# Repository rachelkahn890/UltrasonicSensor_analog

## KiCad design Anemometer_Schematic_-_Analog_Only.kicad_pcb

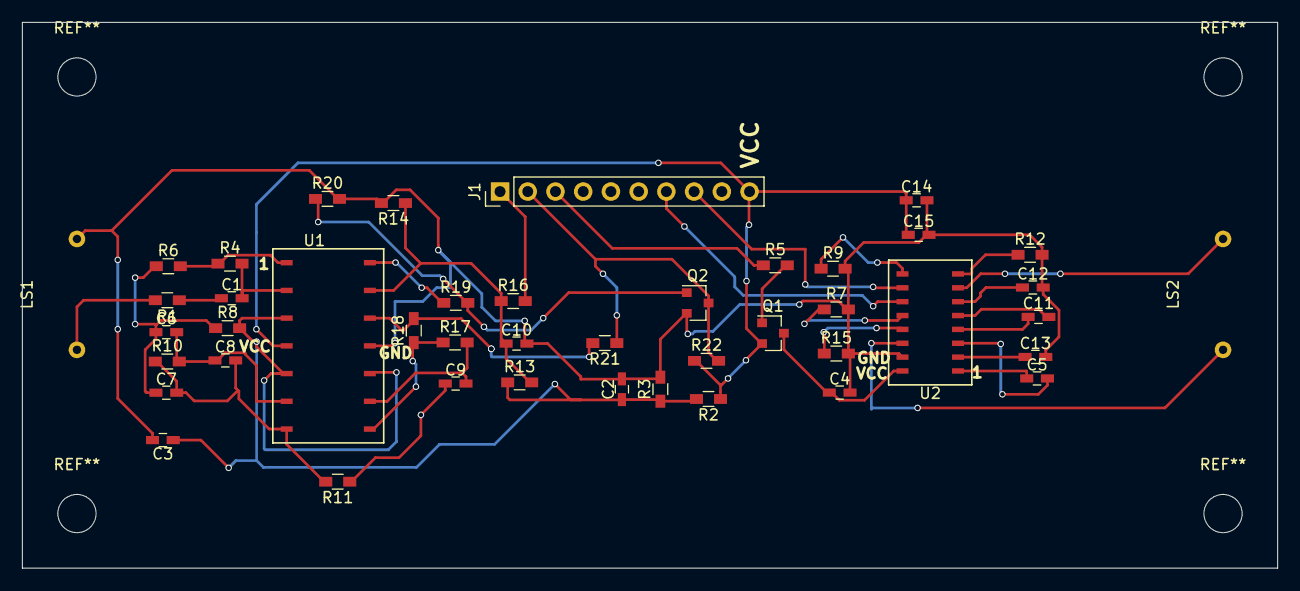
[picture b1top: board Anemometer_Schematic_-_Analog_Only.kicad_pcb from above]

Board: 2 copper layers, 115.0 x 50.0 mm, 44 parts (0 on the bottom side), 36 nets.

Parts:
C1, C9: 10n; C_0603_HandSoldering
C2: 1u2; C_0603_HandSoldering
C3: 150n; C_0603_HandSoldering
C4, C14, C15: 10uF; C_0603_HandSoldering
C5, C11, C12, C13: 1uF; C_0603_HandSoldering
C6, C7: 1n; C_0603_HandSoldering
C8: 12p; C_0603_HandSoldering
C10: CP1_Small; C_0603_HandSoldering
J1: Conn_01x10_Male; Socket_Strip_Straight_1x10_Pitch2.54mm
LS1, LS2: Speaker; ultrasonic_speaker
Q1, Q2: BC857; SOT-23
R1, R7, R9, R11, R12, R15, R22: 10K; R_0603_HandSoldering
R2, R3, R5, R8: 1K; R_0603_HandSoldering
R4: 62K; R_0603_HandSoldering
R6: 6K2; R_0603_HandSoldering
R10: 18k; R_0603_HandSoldering
R13, R21: 120K; R_0603_HandSoldering
R14: 3M3; R_0603_HandSoldering
R16, R17: 75K; R_0603_HandSoldering
R18: 4K53; R_0603_HandSoldering
R19, R20: R; R_0603_HandSoldering
U1: LM324
U2: MAX232; MAX232A

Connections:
GND: C2.2, C3.2, C4.2, C10.2, C12.2, C13.2, C14.2, C15.2, LS1.2, Q2.2, R3.2, R7.2, R9.2, R12.2, R14.2, R15.2, R20.2, U1.11, U2.15
unnamed: C1.1, R1.1
unnamed: C1.2, R4.2, U1.2
unnamed: C2.1, C3.1, R2.2, R3.1, R8.2, R13.1, U1.3, U1.5, U1.10
unnamed: C4.1, Q1.3, U2.16
unnamed: C5.1, U2.1
unnamed: C5.2, U2.3
unnamed: C6.1, C7.1, R6.1, R8.1
unnamed: C6.2, C8.1, R10.2, U1.6
unnamed: C7.2, C8.2, R10.1, R11.2, U1.7
unnamed: C9.1, R11.1
unnamed: C9.2, R17.2, U1.9
unnamed: C10.1, R13.2, R14.1, R16.1, U1.13
unnamed: C11.1, U2.4
unnamed: C11.2, U2.5
unnamed: C12.1, U2.6
unnamed: C13.1, U2.2
unnamed: J1.1, R16.2
unnamed: J1.2, Q2.3, R21.1, R22.2
unnamed: J1.3, R5.1
unnamed: J1.7, U2.11
unnamed: J1.8, U2.10
unnamed: LS1.1, R1.2
unnamed: LS2.1, U2.14
unnamed: LS2.2, U2.7
unnamed: Q1.1, R5.2
unnamed: Q2.1, R19.2, R20.1
unnamed: R4.1, R6.2, U1.1
unnamed: R7.1, U2.12
unnamed: R9.1, U2.9
unnamed: R12.1, U2.8
unnamed: R15.1, U2.13
unnamed: R17.1, R18.1, U1.8
unnamed: R18.2, R21.2, U1.12
unnamed: R19.1, U1.14
VCC: C14.1, C15.1, J1.10, Q1.2, R2.1, R22.1, U1.4

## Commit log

2017-12-19 Adding Kicad files
2017-12-21 Updated: labeled connector on PCB
2018-01-01 PCB draft 2
    Redesigned the PCB to make the layout more optimal. Added VCC and GND connections to U1 in schematic and PCB.
